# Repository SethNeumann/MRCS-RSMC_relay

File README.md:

# REPO NAME: MRCS-RSMC_relay
## License: Creative Commons Attribution-NonCommercial-ShareAlike

Chuck Catania created the Remote Stall Motor Controller for CMRi and cpNode systems to make a single board controller for
common stall motor functions: 
drive (reverse 12V DC to steer the motor) 
Break out Frog power using heavy traces and a 3 position 3.5mm connector
used the second contact to provide power and limiting resistors for indicator LEDs on a panel or dwarf signal 
This board replaces the TC4428 with a DPDT relay to provide a full metallic connection to avoid sneak paths in the FETs.

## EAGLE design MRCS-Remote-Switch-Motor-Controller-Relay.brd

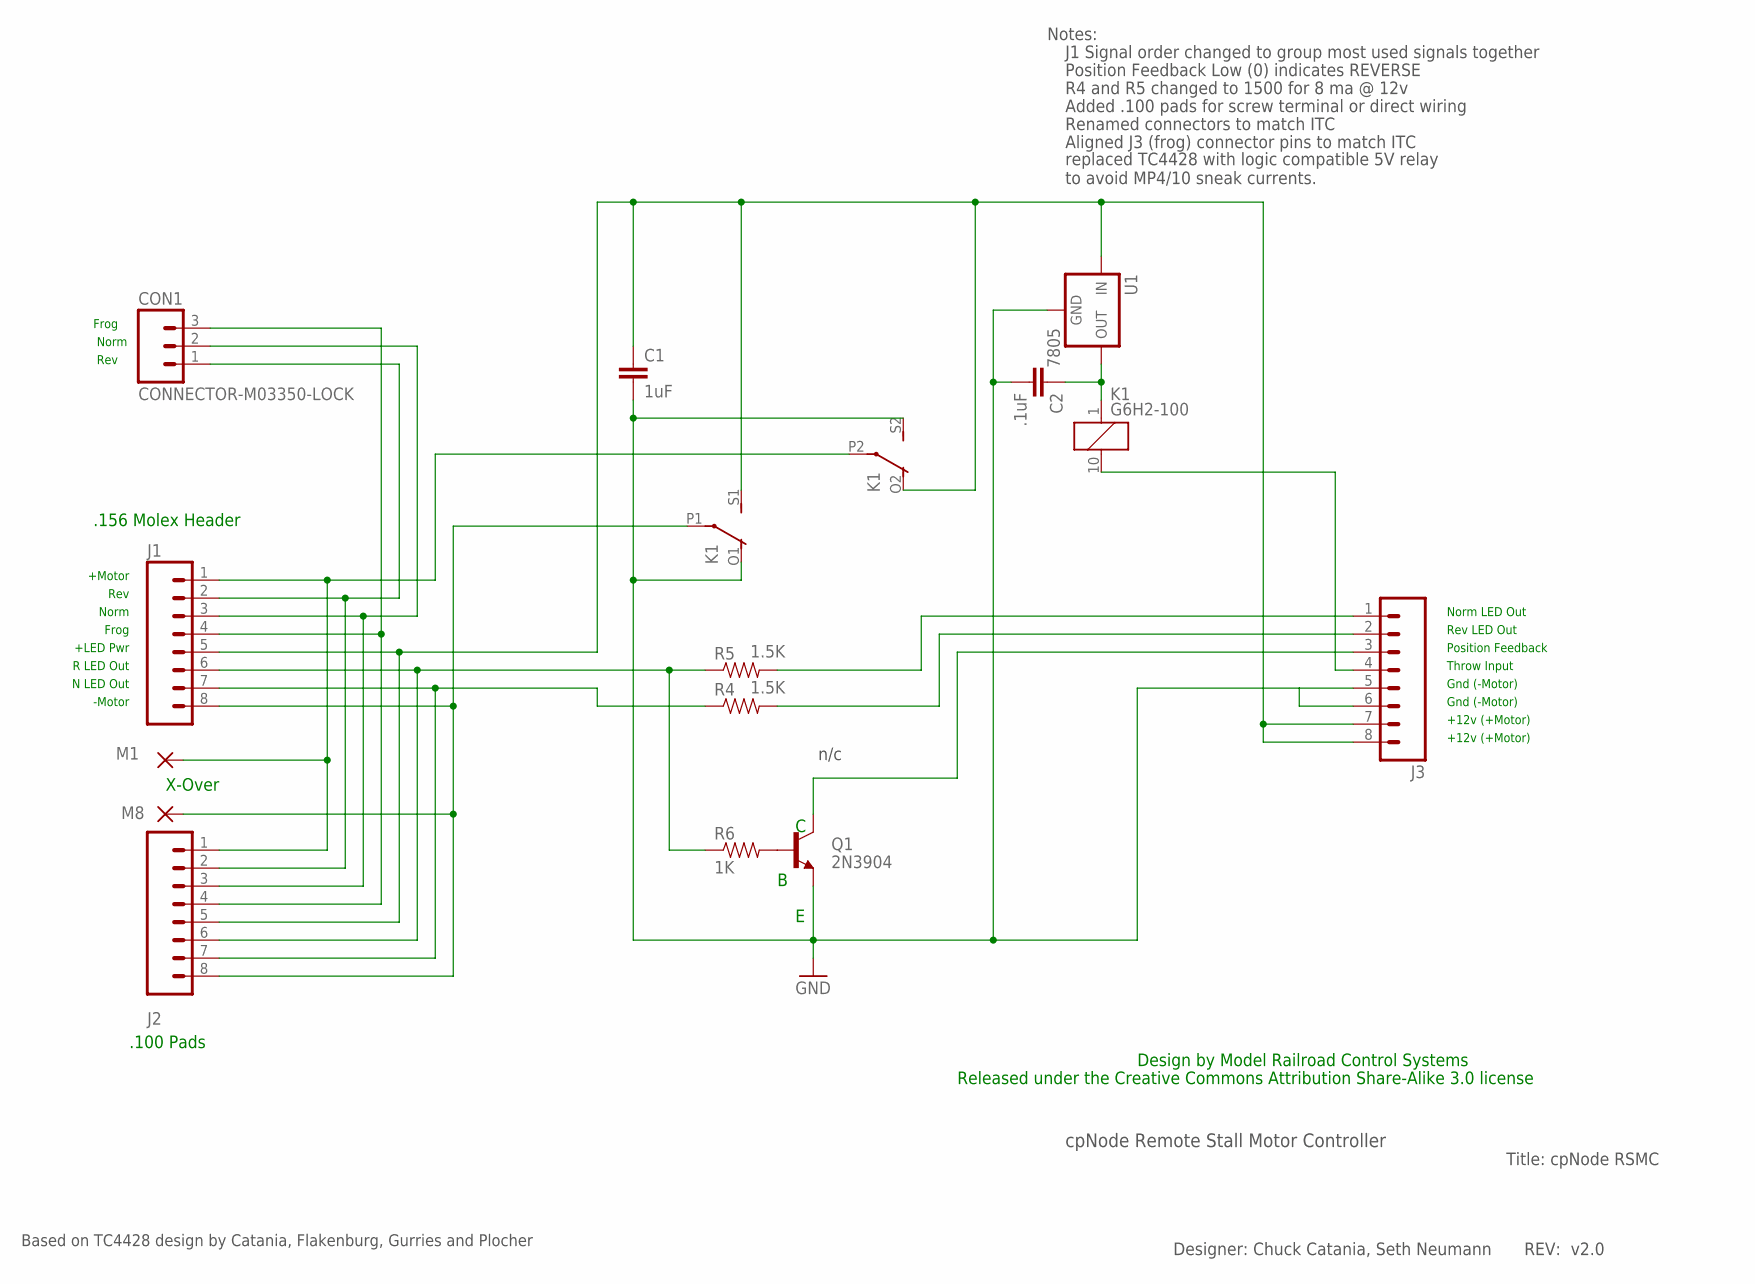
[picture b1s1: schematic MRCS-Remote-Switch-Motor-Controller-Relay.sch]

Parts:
C1: 1uF; CAP-PTH-SMALLEZ
C2: .1uF; CAP-PTH-SMALLEZ
CON1: CONNECTOR-M03350-LOCK; 1751251
J1: J1; KK-156-8-F
J2: J2; 1X08_PIN1_NO_SILK
J3: CONNECTOR-M08LOCK; 1X08_LOCK
K1: G6H2-100
M1, M8: WIREPAD2,54/1,1; 2,54/1,1
Q1: 2N3904; TO-92-MS013
R4, R5: 1.5K; AXIAL-0.4-RES
R6: 1K; AXIAL-0.4-RES
U1: 7805; TO92D-

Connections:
+5: C2.1, K1.1, U1.3 (VOUT)
+12: C1.1, J1.5, J2.5, J3.7, J3.8, K1.O2 (O), K1.S1 (S), U1.1 (VIN)
FROG: CON1.3, J1.4, J2.4
GND: C1.2, C2.2, J3.5, J3.6, K1.O1 (O), K1.S2 (S), Q1.1 (E), U1.2 (GND)
M1: J1.1, J2.1, K1.P2, M1.1
M8: J1.8, J2.8, K1.P1, M8.1
unnamed: J3.3, Q1.3 (C)
unnamed: J3.2, R4.P$2 (2)
unnamed: Q1.2 (B), R6.P$2 (2)
unnamed: J3.1, R5.P$2 (2)
N-LED: J1.7, J2.7, R4.P$1 (1)
NORM: CON1.2, J1.3, J2.3
R-LED: J1.6, J2.6, R5.P$1 (1), R6.P$1 (1)
REV: CON1.1, J1.2, J2.2
THROW: J3.4, K1.10 (2)

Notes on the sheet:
Norm
Rev
+12v (+Motor)
Gnd (-Motor)
Norm LED Out
Rev LED Out
Frog
+Motor
-Motor
Throw Input
+LED Pwr
R LED Out
N LED Out
.156 Molex Header
Position Feedback
cpNode Remote Stall Motor Controller
Title: cpNode RSMC
Designer: Chuck Catania, Seth Neumann
REV: v2.0
n/c
Based on TC4428 design by Catania, Flakenburg, Gurries and Plocher
Notes:
Position Feedback Low (0) indicates REVERSE
R4 and R5 changed to 1500 for 8 ma @ 12v
J1 Signal order changed to group most used signals together
Frog
.100 Pads
Added .100 pads for screw terminal or direct wiring
X-Over
Renamed connectors to match ITC
Aligned J3 (frog) connector pins to match ITC
Released under the Creative Commons Attribution Share-Alike 3.0 license
Design by Model Railroad Control Systems
replaced TC4428 with logic compatible 5V relay to avoid MP4/10 sneak currents.

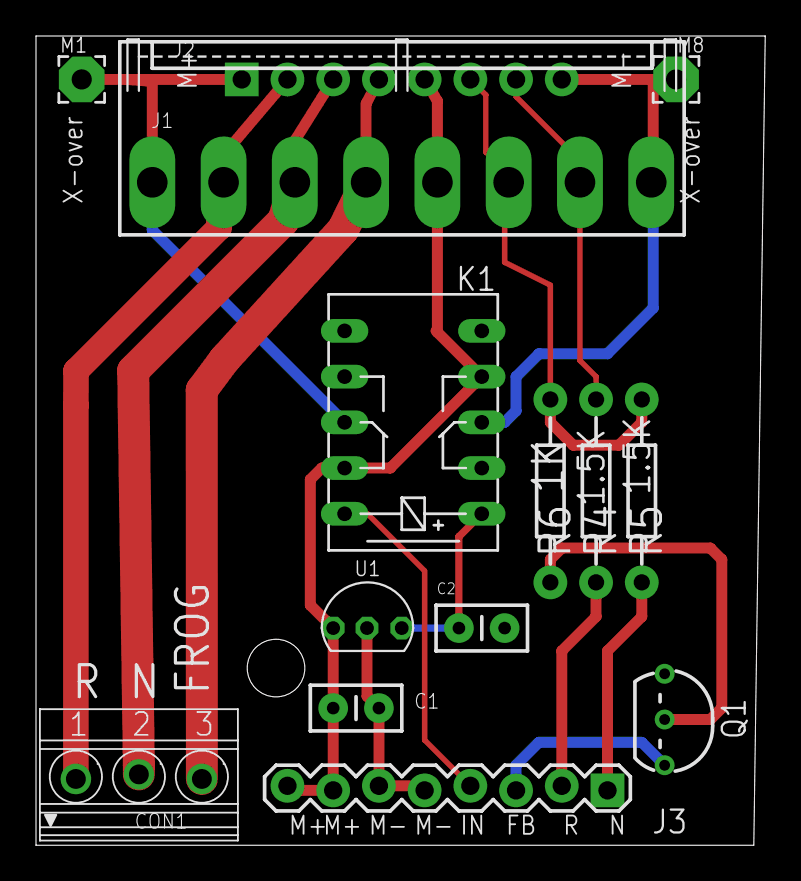
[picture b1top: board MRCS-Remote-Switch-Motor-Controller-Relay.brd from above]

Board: 2 copper layers, 40.5 x 45.0 mm, 16 parts (0 on the bottom side), 15 nets.

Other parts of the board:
U$1: MRCSLOGOBTM
U$2: CA-PROP65WARNING

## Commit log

2026-06-19 Revise DESCRIPTION file for project clarity
    Updated project description to clarify functionality and changes.
2026-06-19 Update project metadata in INFO file
2026-06-19 Revise project description in doc.md
    Updated project description and removed usage instructions.
2026-06-19 Change repository name and license in README
    Updated repository name and license information.
2026-06-19 Update README with project details and remove template
    Removed usage instructions and added project description.
2026-06-19 initial committ
    moved files from off-line directory

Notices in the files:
parts and their libraries:
SparkFun-Connectors: Licensing: CC v3.0 Share-Alike You are welcome to use this library for commercial purposes.
